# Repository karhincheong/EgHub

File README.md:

# Eg USB Hub

A 4-port output USB Hub keychain in the shape of an egg as a tribute to my friends. Main IC being CoreChips SL2.1S

## Motivation

This project is meant to be a try-out project for Fallout. It is to function as a primer for me to learn to make/design a PCB and at the same time make something useful.

## BOM

### Components List

<!-- prettier-ignore-start -->

|Item|Description|Quantity|Unit Price (USD)|Total Price (USD)|URL|Notes|
|---|---|---|---|---|---|---|
|Capacitor|0402 1 uF|16|0.0038|0.380|https://www.lcsc.com/product-detail/C29266.html|MOQ=100|
||0402 100 nF|16|0.0014|0.14|https://www.lcsc.com/product-detail/C14663.html|MOQ=100|
|Resistor|0603 5.1 kΩ|12|0.0016|0.16|https://www.lcsc.com/product-detail/C23186.html|MOQ=100|
|USB-A Receptacle||4|0.0665|0.665|https://www.lcsc.com/product-detail/C668591.html|MOQ=10|
|USB-C Receptacle||6|0.0741|1.482|https://www.lcsc.com/product-detail/C2765186.html|MOQ=20|
|CoreChips SL2.1S ||2|0.2849|1.4245|https://www.lcsc.com/product-detail/C2684433.html|MOQ=5|
|USBLC6-2SC6 ||16|0.154|3.080|https://www.lcsc.com/product-detail/C7519.html|MOQ=20|
|PCB (JLCPCB) Order||1|2.0000|2.0000|https://www.jlcpcb.com|MOQ=5|
||||||||
|TOTAL (for 2 units)||||9.33|||
|Component Cost per Unit||||4.67|||

<!-- prettier-ignore-end -->

### Additional Costs Incurred

| Item     | Description                 | Price (USD) |
| -------- | --------------------------- | ----------- |
| Shipping | UPS Worldwide Express Saver | 9.24        |

## Assembly Instructions

File Structure

| Folder   | Description                                   |
| -------- | --------------------------------------------- |
| `kicad/` | Files generated in KiCAD                      |
| `3d`     | 3D Mechanical Models for the case and the PCB |

1. Print out the top and bottom covers using a 3D Printer.
2. Screw M3 screws into the 3 screw holes to an adequate tightness such that it doesnt damage the USB receptacles. Take note of the postition of the input USB-C.

## Schematic Diagram

## PCB Layout

## PCB Render

## Case Render

## Project Zine

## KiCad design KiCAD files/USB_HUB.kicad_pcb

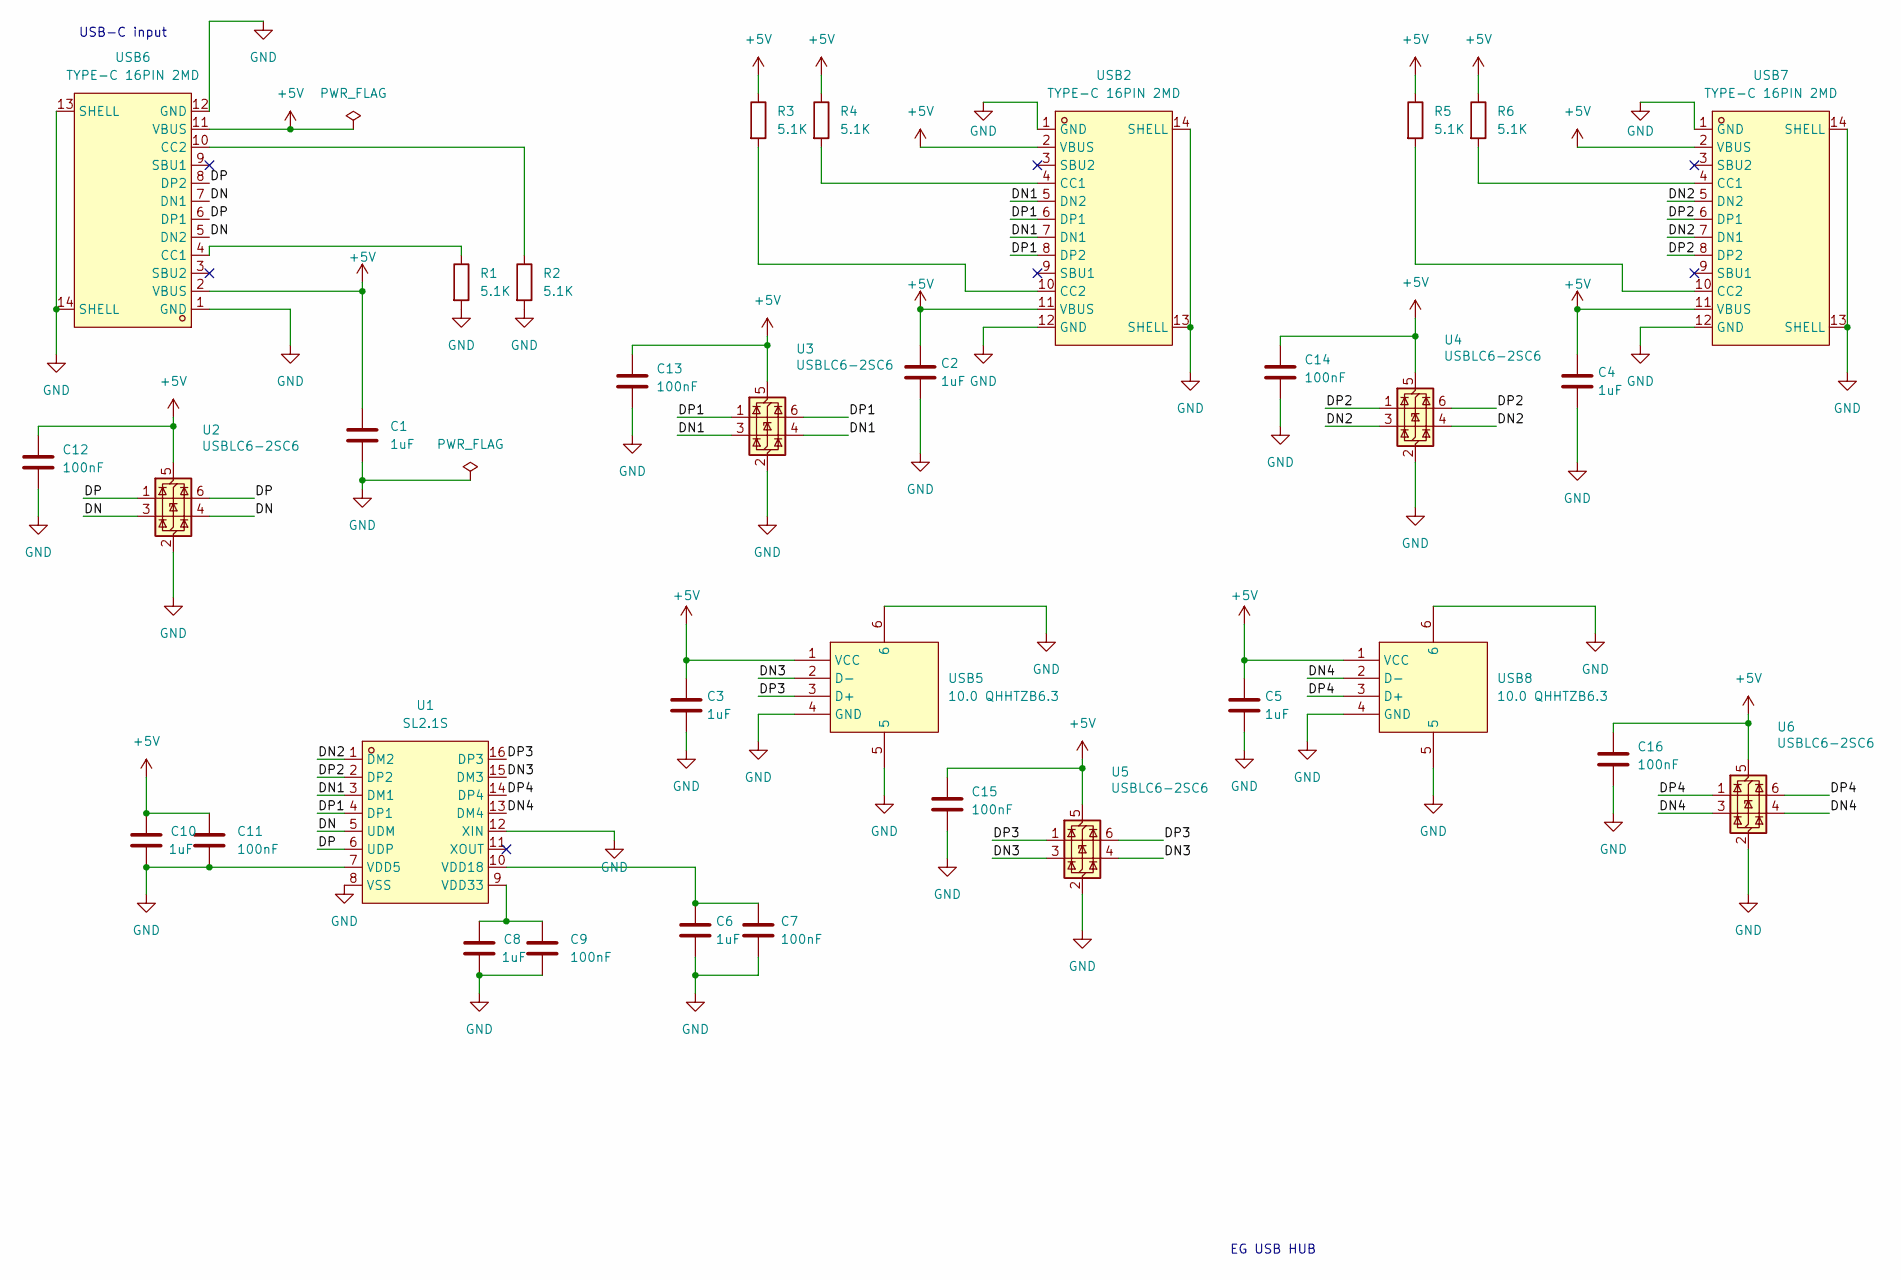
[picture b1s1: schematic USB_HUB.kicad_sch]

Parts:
C1, C2, C3, C4, C5, C6, C8, C10: 1uF; C_0402_1005Metric
C7, C9, C11, C12, C13, C14, C15, C16: 100nF; C_0402_1005Metric
R1, R2, R3, R4, R5, R6: 5.1K; R_0603_1608Metric
U1: SL2.1S; SSOP-16_L4.6-W2.6-P0.53-LS4.0-BL; MPN SL2.1s; LCSC Part C2684433
U2, U3, U4, U5, U6: USBLC6-2SC6; SOT-23-6
USB2, USB6, USB7: TYPE-C 16PIN 2MD; USB-C-SMD_TYPE-C-6PIN-2MD-073; MPN TYPE-C 16PIN 2MD(073); LCSC Part C2765186
USB5, USB8: 10.0 QHHTZB6.3; USB-A-TH_10.0QHHTZB6.3; MPN 10.0 QHHTZB6.3; LCSC Part C668591

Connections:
+5V: C1.1, C2.1, C3.1, C4.1, C5.1, C10.1, C11.1, C12.1, C13.1, C14.1, C15.1, C16.1, R3.1, R4.1, R5.1, R6.1, U2.5 (VBUS), U3.5 (VBUS), U4.5 (VBUS), U5.5 (VBUS), U6.5 (VBUS), USB2.2 (VBUS), USB2.11 (VBUS), USB5.1 (VCC), USB6.2 (VBUS), USB6.11 (VBUS), USB7.2 (VBUS), USB7.11 (VBUS), USB8.1 (VCC)
/DN: U1.5 (UDM), U2.3 (I/O2), U2.4 (I/O2), USB6.5 (DN2), USB6.7 (DN1)
/DN1: U1.3 (DM1), U3.3 (I/O2), U3.4 (I/O2), USB2.5 (DN2), USB2.7 (DN1)
/DN2: U1.1 (DM2), U4.3 (I/O2), U4.4 (I/O2), USB7.5 (DN2), USB7.7 (DN1)
/DN3: U1.15 (DM3), U5.3 (I/O2), U5.4 (I/O2), USB5.2 (D-)
/DN4: U1.13 (DM4), U6.3 (I/O2), U6.4 (I/O2), USB8.2 (D-)
/DP: U1.6 (UDP), U2.1 (I/O1), U2.6 (I/O1), USB6.6 (DP1), USB6.8 (DP2)
/DP1: U1.4 (DP1), U3.1 (I/O1), U3.6 (I/O1), USB2.6 (DP1), USB2.8 (DP2)
/DP2: U1.2 (DP2), U4.1 (I/O1), U4.6 (I/O1), USB7.6 (DP1), USB7.8 (DP2)
/DP3: U1.16 (DP3), U5.1 (I/O1), U5.6 (I/O1), USB5.3 (D+)
/DP4: U1.14 (DP4), U6.1 (I/O1), U6.6 (I/O1), USB8.3 (D+)
GND: C1.2, C2.2, C3.2, C4.2, C5.2, C6.2, C7.2, C8.2, C9.2, C10.2, C11.2, C12.2, C13.2, C14.2, C15.2, C16.2, R1.2, R2.2, U1.7 (VDD5), U1.8 (VSS), U1.12 (XIN), U2.2 (GND), U3.2 (GND), U4.2 (GND), U5.2 (GND), U6.2 (GND), USB2.1 (GND), USB2.12 (GND), USB2.13 (SHELL), USB2.14 (SHELL), USB5.4 (GND), USB5.5, USB5.6, USB6.1 (GND), USB6.12 (GND), USB6.13 (SHELL), USB6.14 (SHELL), USB7.1 (GND), USB7.12 (GND), USB7.13 (SHELL), USB7.14 (SHELL), USB8.4 (GND), USB8.5, USB8.6
unnamed: C6.1, C7.1, U1.10 (VDD18)
unnamed: C8.1, C9.1, U1.9 (VDD33)
unnamed: R4.2, USB2.4 (CC1)
unnamed: R3.2, USB2.10 (CC2)
unnamed: R1.1, USB6.4 (CC1)
unnamed: R2.1, USB6.10 (CC2)
unnamed: R6.2, USB7.4 (CC1)
unnamed: R5.2, USB7.10 (CC2)

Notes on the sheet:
EG USB HUB
USB-C input

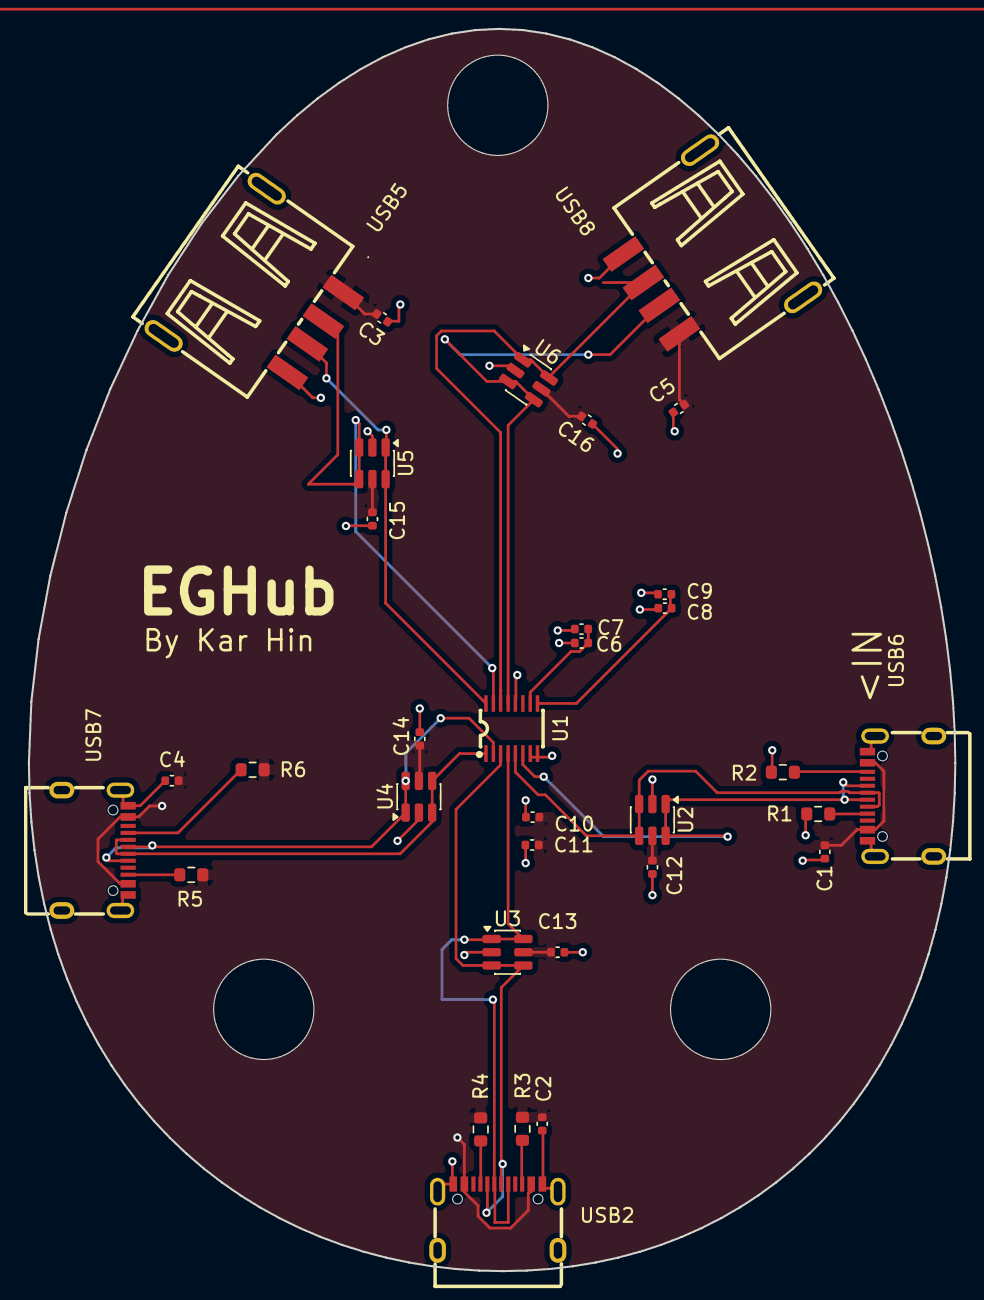
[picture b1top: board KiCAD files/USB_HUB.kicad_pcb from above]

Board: 2 copper layers, 66.5 x 89.2 mm, 33 parts (0 on the bottom side), 20 nets.

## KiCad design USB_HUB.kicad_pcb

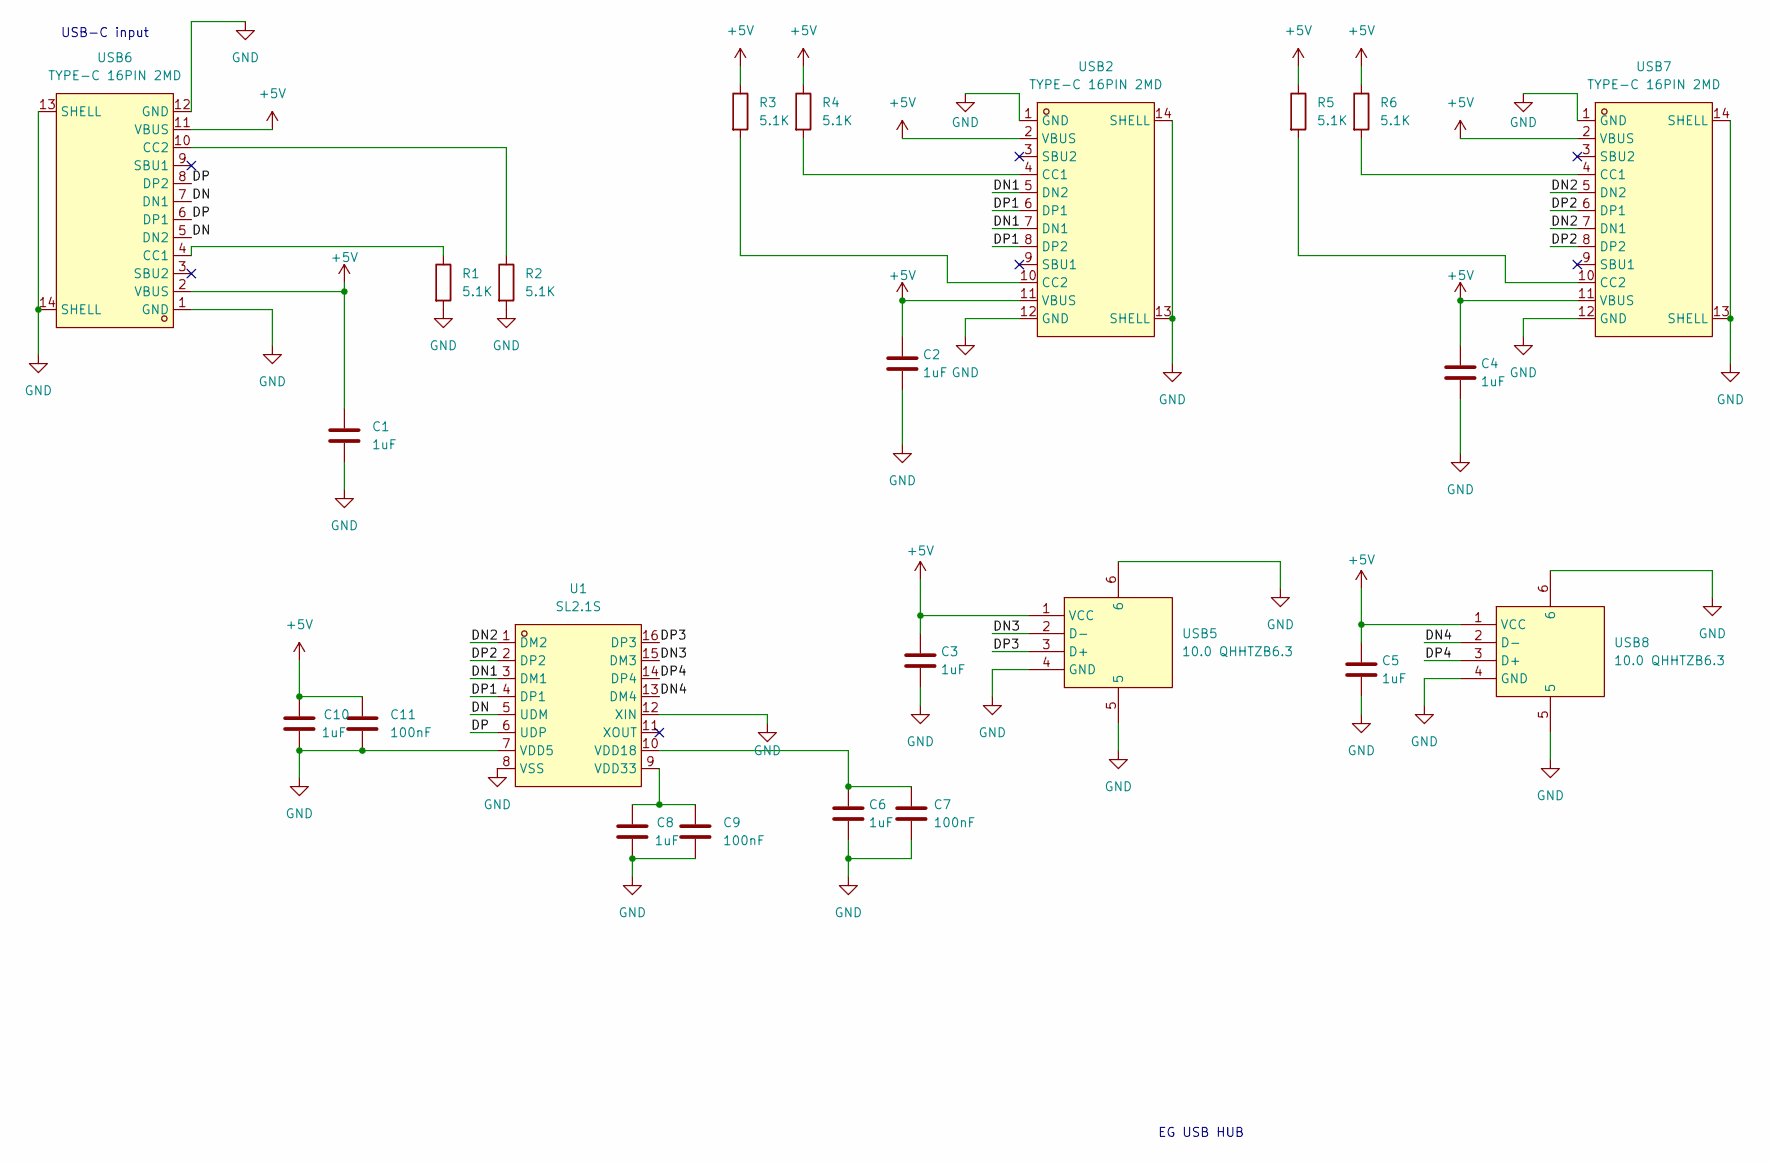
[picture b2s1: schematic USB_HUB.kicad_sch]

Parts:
C1, C2, C3, C4, C5, C6, C8, C10: 1uF; C_0402_1005Metric
C7, C9, C11: 100nF; C_0402_1005Metric
R1, R2, R3, R4, R5, R6: 5.1K; R_0603_1608Metric
U1: SL2.1S; SSOP-16_L4.6-W2.6-P0.53-LS4.0-BL; MPN SL2.1s; LCSC Part C2684433
USB2, USB6, USB7: TYPE-C 16PIN 2MD; USB-C-SMD_TYPE-C-6PIN-2MD-073; MPN TYPE-C 16PIN 2MD(073); LCSC Part C2765186
USB5, USB8: 10.0 QHHTZB6.3; USB-A-TH_10.0QHHTZB6.3; MPN 10.0 QHHTZB6.3; LCSC Part C668591

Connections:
+5V: C1.1, C2.1, C3.1, C4.1, C5.1, C10.1, C11.1, R3.1, R4.1, R5.1, R6.1, USB2.2 (VBUS), USB2.11 (VBUS), USB5.1 (VCC), USB6.2 (VBUS), USB6.11 (VBUS), USB7.2 (VBUS), USB7.11 (VBUS), USB8.1 (VCC)
/DN: U1.5 (UDM), USB6.5 (DN2), USB6.7 (DN1)
/DN1: U1.3 (DM1), USB2.5 (DN2), USB2.7 (DN1)
/DN2: U1.1 (DM2), USB7.5 (DN2), USB7.7 (DN1)
/DN3: U1.15 (DM3), USB5.2 (D-)
/DN4: U1.13 (DM4), USB8.2 (D-)
/DP: U1.6 (UDP), USB6.6 (DP1), USB6.8 (DP2)
/DP1: U1.4 (DP1), USB2.6 (DP1), USB2.8 (DP2)
/DP2: U1.2 (DP2), USB7.6 (DP1), USB7.8 (DP2)
/DP3: U1.16 (DP3), USB5.3 (D+)
/DP4: U1.14 (DP4), USB8.3 (D+)
GND: C1.2, C2.2, C3.2, C4.2, C5.2, C6.2, C7.2, C8.2, C9.2, C10.2, C11.2, R1.2, R2.2, U1.7 (VDD5), U1.8 (VSS), U1.12 (XIN), USB2.1 (GND), USB2.12 (GND), USB2.13 (SHELL), USB2.14 (SHELL), USB5.4 (GND), USB5.5, USB5.6, USB6.1 (GND), USB6.12 (GND), USB6.13 (SHELL), USB6.14 (SHELL), USB7.1 (GND), USB7.12 (GND), USB7.13 (SHELL), USB7.14 (SHELL), USB8.4 (GND), USB8.5, USB8.6
unnamed: C6.1, C7.1, U1.10 (VDD18)
unnamed: C8.1, C9.1, U1.9 (VDD33)
unnamed: R4.2, USB2.4 (CC1)
unnamed: R3.2, USB2.10 (CC2)
unnamed: R1.1, USB6.4 (CC1)
unnamed: R2.1, USB6.10 (CC2)
unnamed: R6.2, USB7.4 (CC1)
unnamed: R5.2, USB7.10 (CC2)

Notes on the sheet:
EG USB HUB
USB-C input

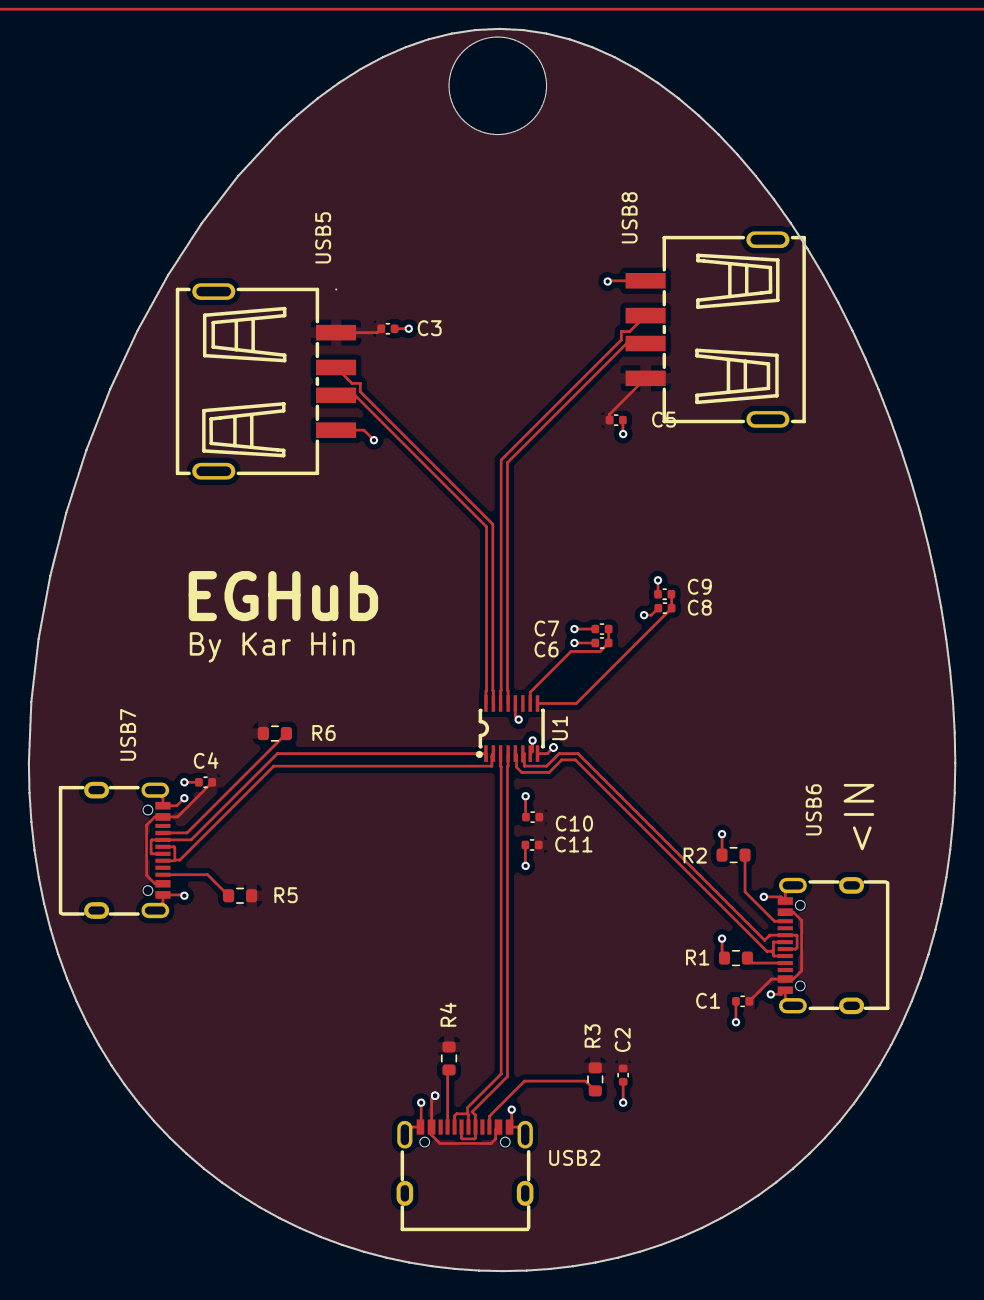
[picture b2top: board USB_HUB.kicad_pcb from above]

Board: 2 copper layers, 66.5 x 89.2 mm, 23 parts (0 on the bottom side), 20 nets.

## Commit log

2026-05-31 Fixed Readme and Zine
2026-05-31 Added Zine
2026-05-31 Reorganised FIles
2026-06-10 Updated board design to include ESD. Not changed: Zine, README except BOM
2026-06-13 Fixes to review requirements check
2026-06-13 changed folder name for req check warnings
2026-06-13 Changed readme to include detailed assembly instructions
2026-06-14 Readded Gerber Files
